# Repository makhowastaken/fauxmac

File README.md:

# fauxmac
Romac+ Macro Pad remade because the original is no longer for sale

It should use the same firmware as the official QMK repo Romac+ but things may have to be tweaked slightly. Uses a LED strip instead of four SMT RGB LEDs soldered to the bottom. You can use as many as you want but make sure to tweak the firmware if you use more than four. 

Case sizing IS different. I don't know what the original is sized at but mine is sized 83.8mm wide by 88.0mm tall. Mounting hole spacing is 77.8mm wide by 82.0mm tall. Key spacing is 19.0mm 

I exported the board to a SVG to assist with case design

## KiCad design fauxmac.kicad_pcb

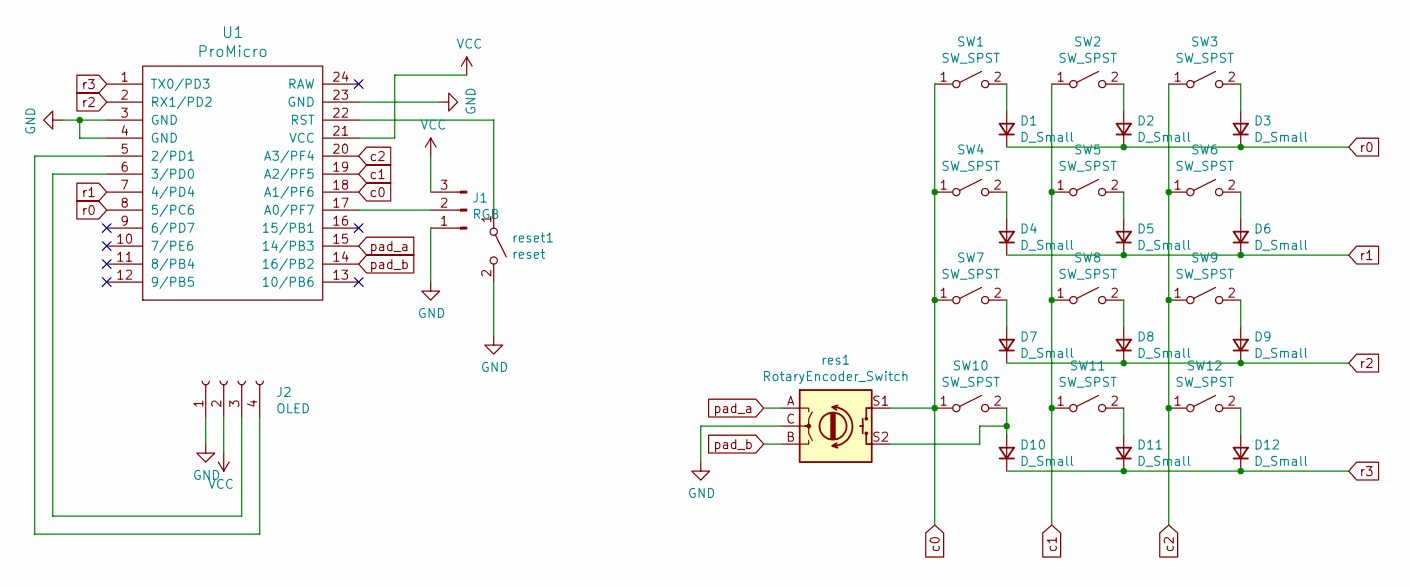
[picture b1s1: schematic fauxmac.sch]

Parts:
D1, D2, D3, D4, D5, D6, D7, D8, D9, D10, D11, D12: D_Small; D3_TH_SMD_back_only
J1: RGB; StripLED_rev_frontonly
J2: OLED; PinHeader_1x04_P2.54mm_Vertical
SW1, SW2, SW3, SW4, SW5, SW6, SW7, SW8, SW9, SW10, SW11, SW12: SW_SPST; MX-Alps-Choc-1U-NoLED
U1: ProMicro; ArduinoProMicro-ZigZag_back_silk_removed
res1: RotaryEncoder_Switch; RotaryEncoder_EC11
reset1: reset; SW_Tactile_SPST_Angled_MJTP1117

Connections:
GND: J1.1, J2.1, U1.3 (GND), U1.4 (GND), U1.23 (GND), res1.C, reset1.2 (B)
unnamed: D1.2 (A), SW1.2 (B)
unnamed: D2.2 (A), SW2.2 (B)
unnamed: D3.2 (A), SW3.2 (B)
unnamed: D4.2 (A), SW4.2 (B)
unnamed: D5.2 (A), SW5.2 (B)
unnamed: D6.2 (A), SW6.2 (B)
unnamed: D7.2 (A), SW7.2 (B)
unnamed: D8.2 (A), SW8.2 (B)
unnamed: D9.2 (A), SW9.2 (B)
unnamed: D10.2 (A), SW10.2 (B), res1.S2
unnamed: D11.2 (A), SW11.2 (B)
unnamed: D12.2 (A), SW12.2 (B)
unnamed: J1.2, U1.17 (A0/PF7)
unnamed: J2.3, U1.6 (3/PD0)
unnamed: J2.4, U1.5 (2/PD1)
unnamed: U1.22 (RST), reset1.1 (A)
VCC: J1.3, J2.2, U1.21 (VCC)
c0: SW1.1 (A), SW4.1 (A), SW7.1 (A), SW10.1 (A), U1.18 (A1/PF6), res1.S1
c1: SW2.1 (A), SW5.1 (A), SW8.1 (A), SW11.1 (A), U1.19 (A2/PF5)
c2: SW3.1 (A), SW6.1 (A), SW9.1 (A), SW12.1 (A), U1.20 (A3/PF4)
pad_a: U1.15 (14/PB3), res1.A
pad_b: U1.14 (16/PB2), res1.B
r0: D1.1 (K), D2.1 (K), D3.1 (K), U1.8 (5/PC6)
r1: D4.1 (K), D5.1 (K), D6.1 (K), U1.7 (4/PD4)
r2: D7.1 (K), D8.1 (K), D9.1 (K), U1.2 (RX1/PD2)
r3: D10.1 (K), D11.1 (K), D12.1 (K), U1.1 (TX0/PD3)

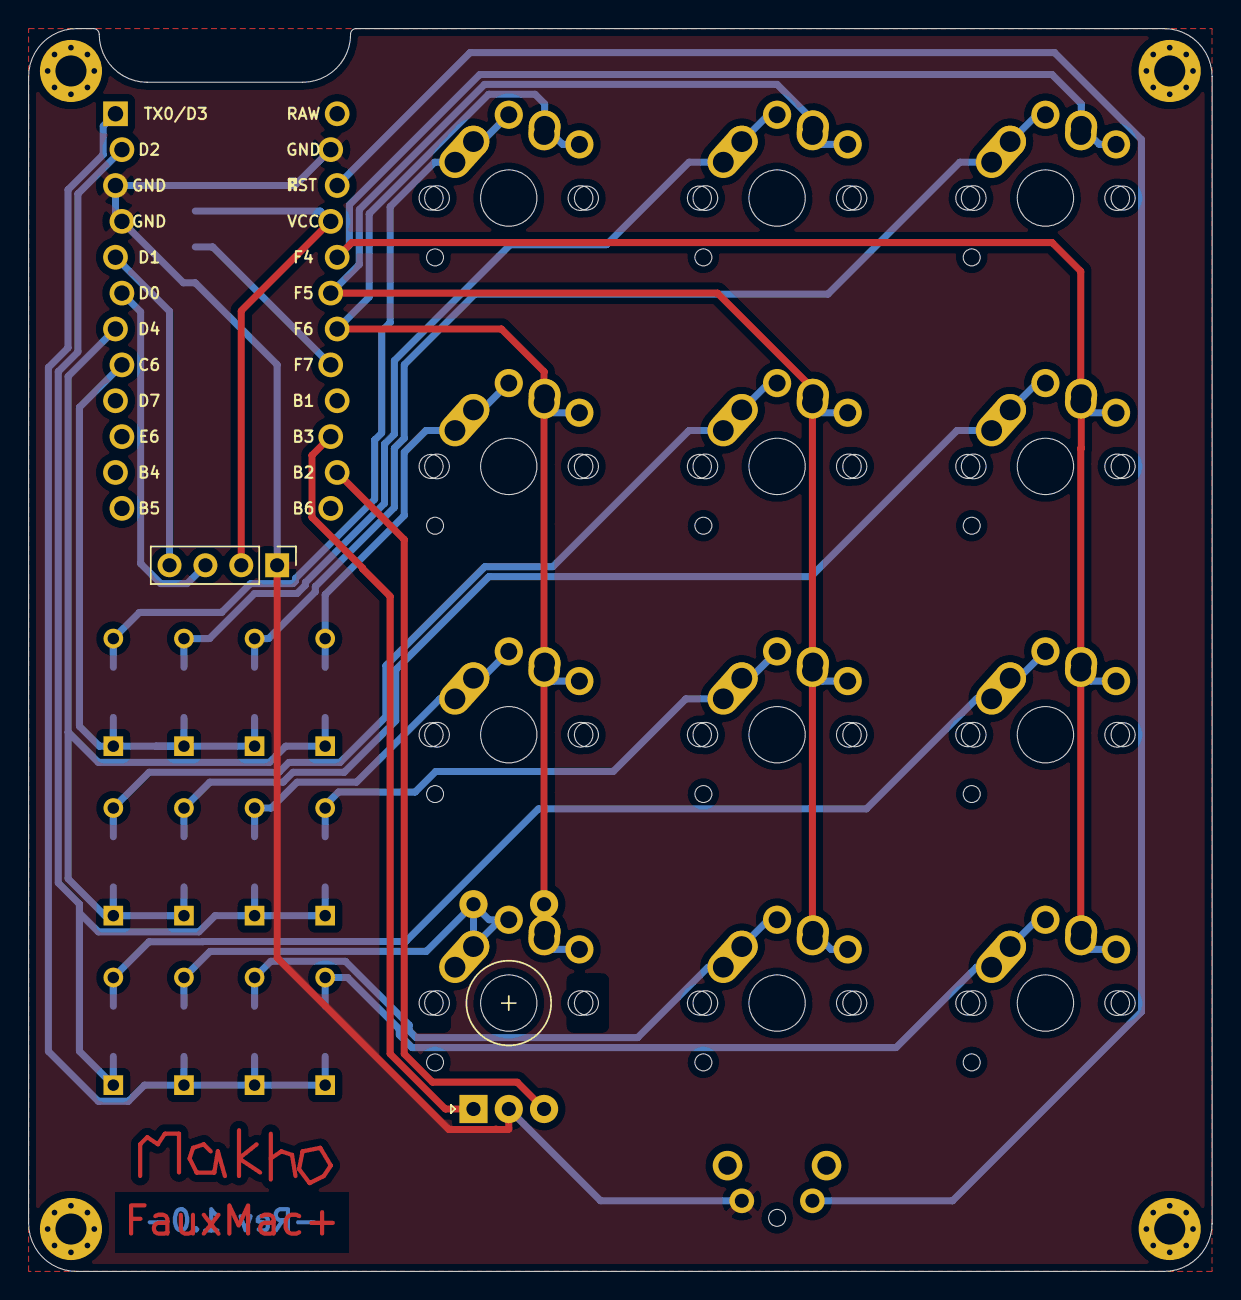
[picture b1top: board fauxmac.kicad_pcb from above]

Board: 2 copper layers, 83.8 x 88.0 mm, 29 parts (1 on the bottom side), 27 nets.

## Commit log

2021-02-14 Rename CC_BY-NC-SA_4.0.txt to license
